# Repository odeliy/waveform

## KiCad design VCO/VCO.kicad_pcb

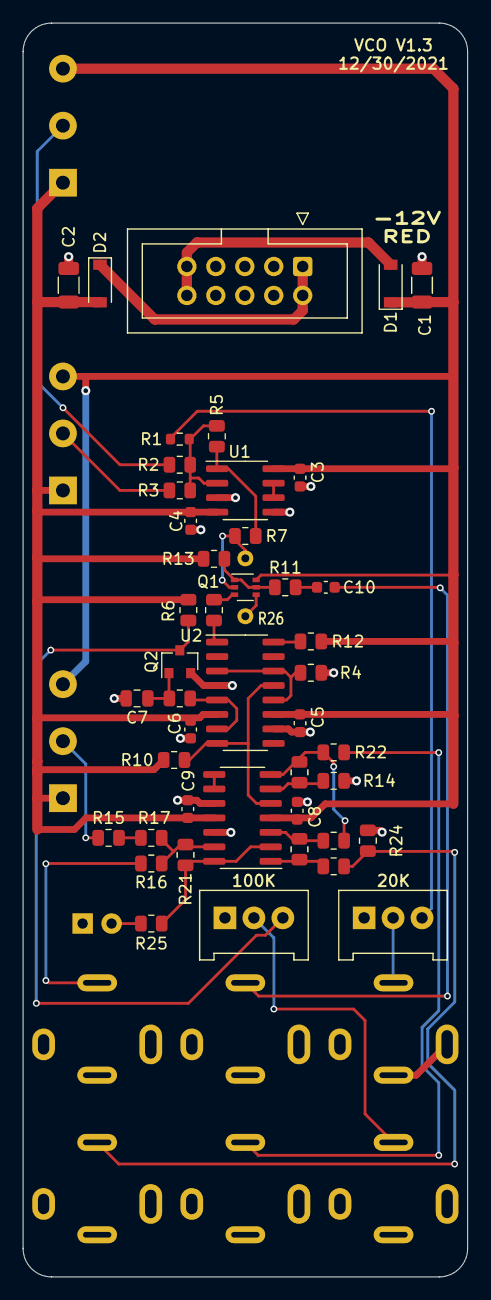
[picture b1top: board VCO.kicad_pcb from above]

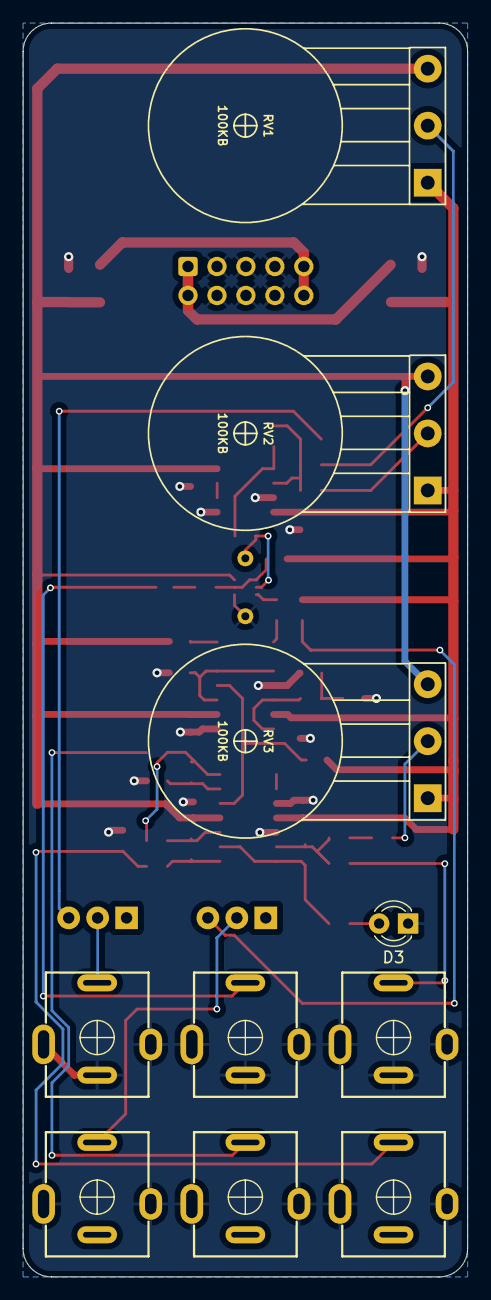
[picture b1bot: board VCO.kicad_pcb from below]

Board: 2 copper layers, 39.0 x 110.0 mm, 56 parts (10 on the bottom side), 38 nets.

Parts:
C1, C2: 10uF; C_1206_3216Metric
C3, C4, C5, C6, C8, C9, C10: 100nF; C_0603_1608Metric
C7: 3.3nF*; C_0805_2012Metric
D1, D2: SCH; D_SOD-123
D3: LED; LED_D3.0mm
J1: PWM; AudioJack_QingPu_WQP-PJ301BM_Vertical
J2: 1V_A; AudioJack_QingPu_WQP-PJ301BM_Vertical
J3: FM; AudioJack_QingPu_WQP-PJ301BM_Vertical
J4: SYNC; AudioJack_QingPu_WQP-PJ301BM_Vertical
J5: POWER; IDC-Header_2x05_P2.54mm_Vertical
J6: TRI; AudioJack_QingPu_WQP-PJ301BM_Vertical
J7: SQR; AudioJack_QingPu_WQP-PJ301BM_Vertical
Q1: BC847BPN; SOT-363_SC-70-6
Q2: MMBFJ112; SOT-23
R1: 91K; R_0603_1608Metric
R2: 330K; R_0805_2012Metric
R3: 10M; R_0805_2012Metric
R4: 5.6K; R_0805_2012Metric
R5, R6, R11, R21: 100K; R_0805_2012Metric
R7, R16: 56K; R_0805_2012Metric
R8, R15, R19: 12K; R_0805_2012Metric
R9: 680R; R_0805_2012Metric
R10, R14, R18: 10K; R_0805_2012Metric
R12: 47K; R_0805_2012Metric
R13, R20: 1M; R_0805_2012Metric
R17: 220K; R_0805_2012Metric
R22: 1K; R_0805_2012Metric
R23, R24, R25: 2K; R_0805_2012Metric
R26: 1K$; Specialty_tempco_paradox
RV1, RV2, RV3: 100KB; POT_16mm_detailed
RV4: 100KT*; TRIM_3296W_Alt
RV5: 20KT*; TRIM_3296W_Alt
U1: TL072; SOIC-8_3.9x4.9mm_P1.27mm
U2: LM13700; SOIC-16_3.9x9.9mm_P1.27mm
U3: TL074; SOIC-14_3.9x8.7mm_P1.27mm

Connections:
+12V: C1.1, C3.1, C5.1, C8.1, D1.1 (K), Q1.6 (C1), R12.1, RV1.3, RV2.3, RV3.3, U1.8 (V+), U2.11 (V+), U3.4 (V+)
-12V: C2.2, C4.2, C6.2, C9.2, D2.2 (A), R6.1, R10.2, R13.2, RV1.1, RV2.1, RV3.1, U1.4 (V-), U2.6 (V-), U3.11 (V-)
/1V_A: J2.T, RV5.2
/FINE: R3.2, RV2.2
/FM_lin: C10.2, J3.T
/FREQ: R2.2, RV1.2
/Iabc: Q1.3 (C2), R8.1
/LED: R21.1, R25.2, U3.2 (-), U3.14
/PW: R15.2, RV3.2
/PWM: J1.T, R16.2
/SQR: J7.T, R23.1, R24.2
/SYNC: J4.T, RV4.2
/TRI: J6.T, R22.1
/TRI_raw: R10.1, U2.8, U2.13 (-), U3.5 (+)
/V_expo: Q1.2 (B1), R7.1, R26.2
/tri2sqr: R18.2, R19.1, R22.2, U3.7
GND: C1.2, C2.1, C3.2, C4.1, C5.2, C6.1, C7.2, C8.2, C9.1, D3.1 (K), J1.S, J1.TN, J2.S, J2.TN, J3.S, J3.TN, J4.S, J5.3, J5.4, J5.5, J5.6, J5.7, J5.8, J6.S, J7.S, Q1.4 (E2), Q2.2 (S), R4.2, R14.2, R24.1, R26.1, U1.3 (+), U1.5 (+), U2.4 (-), U2.10, U3.10 (+), U3.12 (+)
unnamed: C7.1, Q2.1 (D), R9.2
unnamed: C10.1, R11.1
unnamed: D1.2 (A), J5.9, J5.10
unnamed: D2.1 (K), J5.1, J5.2
unnamed: D3.2 (A), R25.1
unnamed: Q1.1 (E1), Q1.5 (B2), R11.2, R13.1
unnamed: Q2.3 (G), R6.2, RV4.3
unnamed: R1.1, R2.1, R3.1, R5.2, U1.2 (-)
unnamed: R1.2, RV5.3
unnamed: R4.1, U2.3 (+), U2.12, U2.14 (+)
unnamed: R5.1, R7.2, U1.1
unnamed: R8.2, U2.1
unnamed: R9.1, U2.5, U2.7
unnamed: R12.2, U2.16
unnamed: R14.1, R19.2, U3.6 (-)
unnamed: R15.1, R17.2
unnamed: R16.1, R17.1, R21.2, U3.13 (-)
unnamed: R18.1, R20.2, U3.3 (+)
unnamed: R20.1, R23.2, U3.1
unnamed: U1.6 (-), U1.7
unnamed: U3.8, U3.9 (-)

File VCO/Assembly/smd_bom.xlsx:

Comment | Designator | Footprint | Part Ref.
100K | R5,R21,R11,R6 | R_0805_2012Metric | C17407
91K | R1 | R_0805_2012Metric | C137484
56K | R7,R16 | R_0805_2012Metric | C17756
2K | R25,R24,R23 | R_0805_2012Metric | C17604
1K | R22 | R_0805_2012Metric | C17513
1M | R20,R13 | R_0805_2012Metric | C17514
12K | R19,R15,R8 | R_0805_2012Metric | C17444
10K | R18,R14,R10 | R_0805_2012Metric | C17414
220K | R17 | R_0805_2012Metric | C17556
47K | R12 | R_0805_2012Metric | C17713
680R | R9 | R_0805_2012Metric | C17798
5.6K | R4 | R_0805_2012Metric | C4382
10M | R3 | R_0805_2012Metric | C26108
330K | R2 | R_0805_2012Metric | C17629
330pF | C11,C12 | C_0805_2012Metric | C51207
4.7pF | C13 | C_0805_2012Metric | C1820
100nF | C10,C9,C8,C6,C5,C4,C3 | C_0603 | C14663
3.3nF* | C7 | C_0805_2012Metric | C76473
10uF | C2,C1 | C_1206_3216Metric | C13585
BC847BPN | Q1 | SOT-363_SC-70-6 | C8655
MMBFJ112 | Q2 | SOT-23 | C258195
SCH | D2,D1 | D_SOD-123 | C8598
TL072 | U1 | SOIC-8_3.9x4.9mm_P1.27mm | C6961
TL074 | U3 | SOIC-14_3.9x8.7mm_P1.27mm | C12594
LM13700 | U2 | SOIC-16_3.9x9.9mm_P1.27mm | C174050

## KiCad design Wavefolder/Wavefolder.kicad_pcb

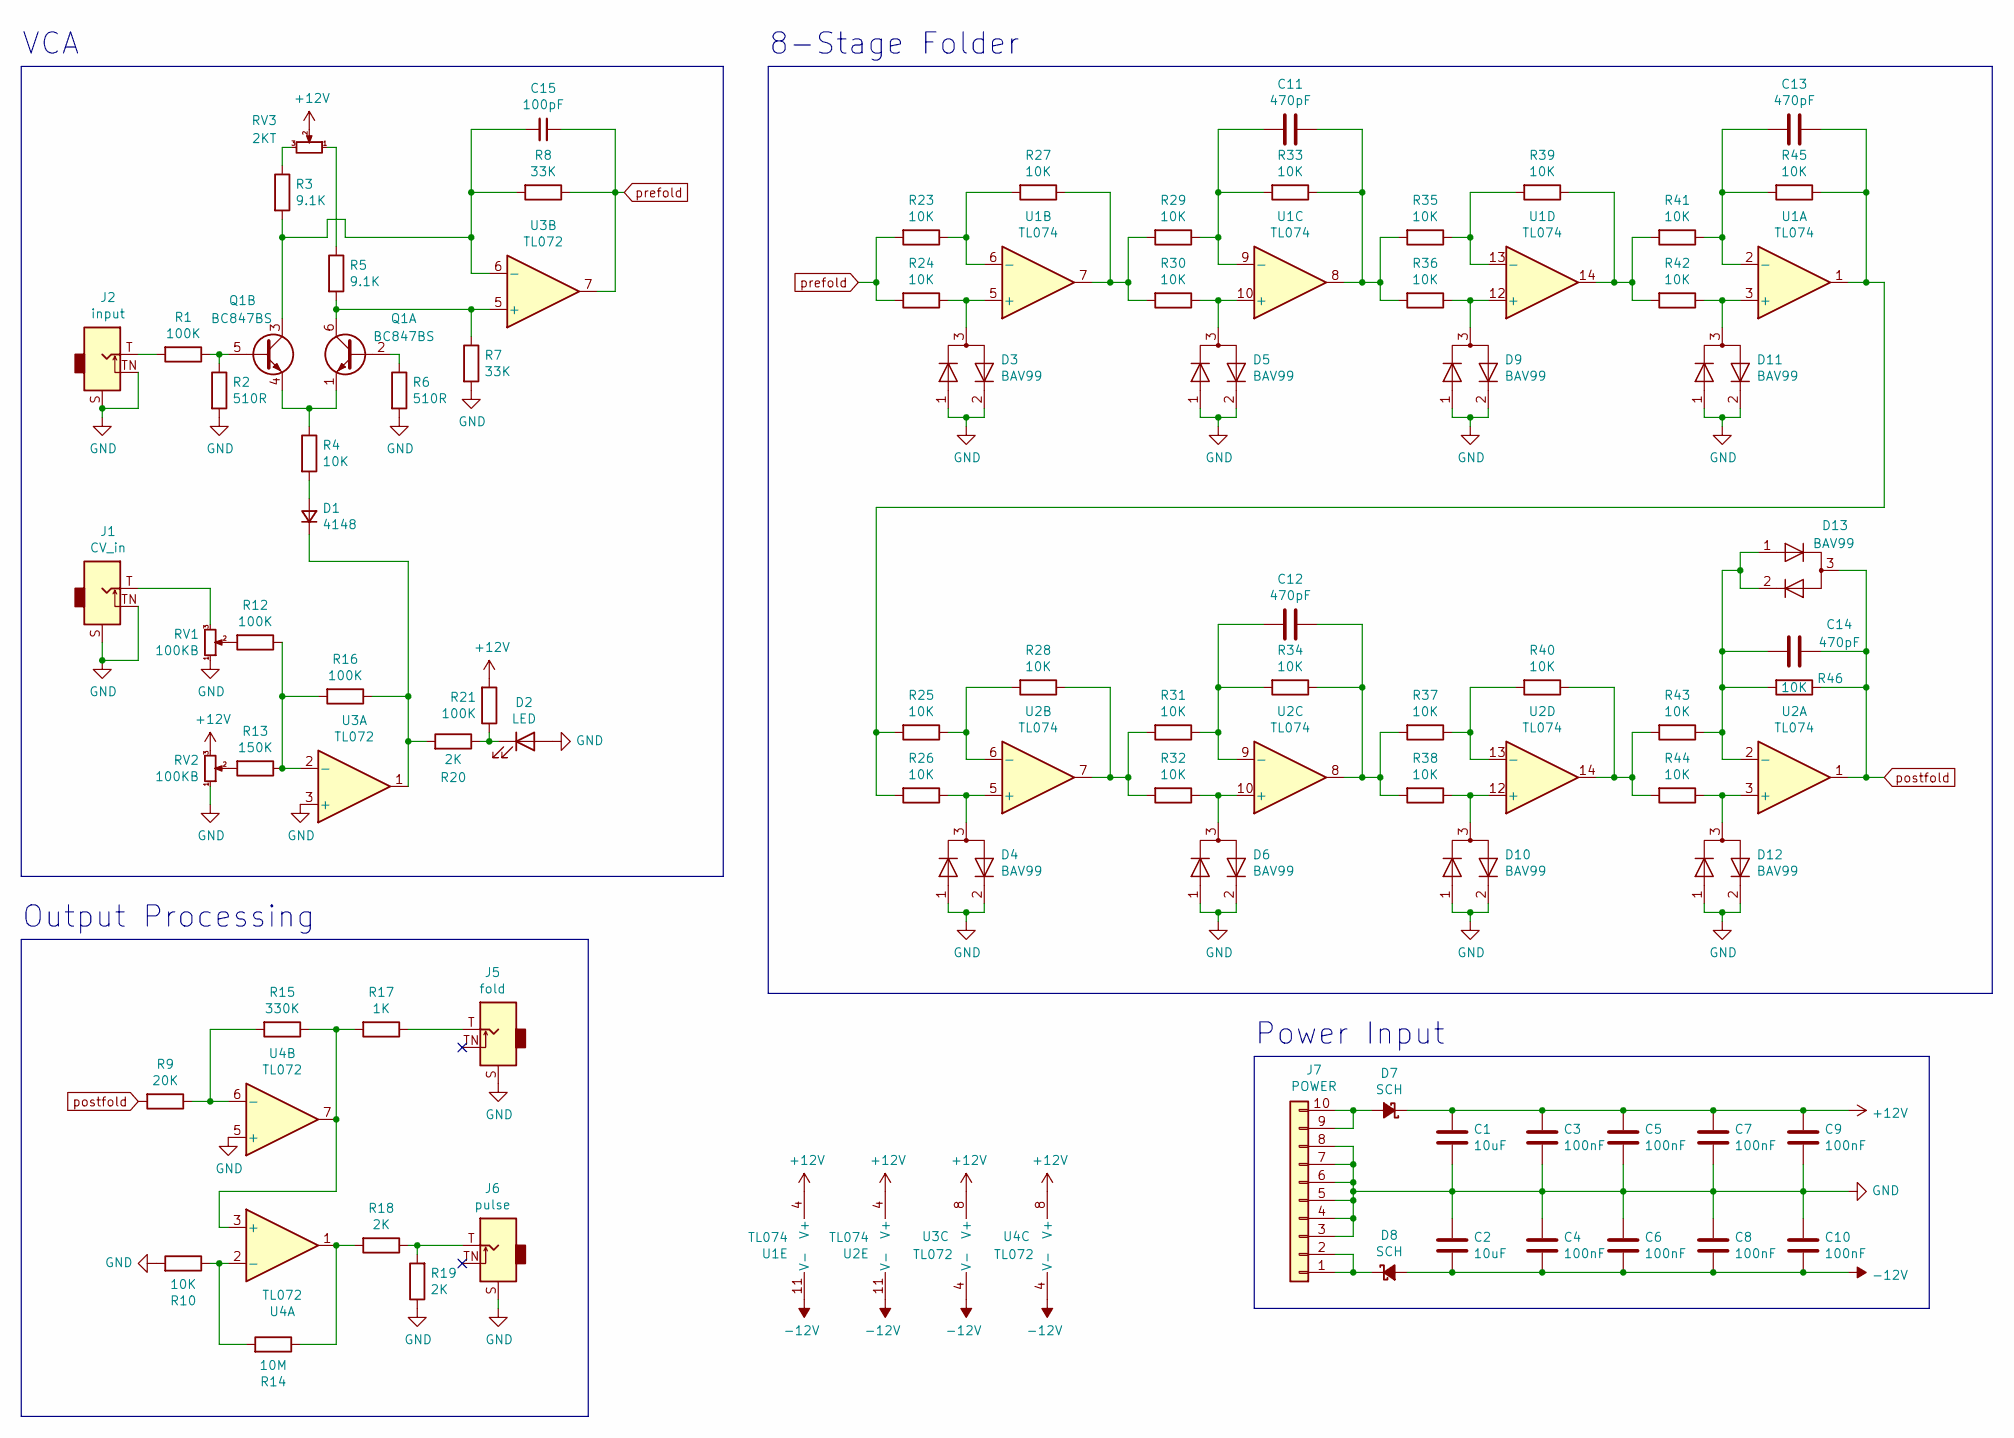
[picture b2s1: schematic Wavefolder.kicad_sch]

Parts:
C1, C2: 10uF; C_1206_3216Metric
C3, C4, C5, C6, C7, C8, C9, C10: 100nF; C_0603_1608Metric
C11, C12, C13, C14: 470pF; C_0805_2012Metric
C15: 100pF; C_0805_2012Metric
D1: 4148; D_SOD-123
D2: LED; LED_3mm
D3: BAV99; SOT-23; Part Ref C2500
D4, D5, D6, D9, D10, D11, D12, D13: BAV99; SOT-23; Part Ref C29718
D7, D8: SCH; D_SOD-123
J1: CV_in; AudioJack_QuPing_Pushfit
J2: input; AudioJack_QuPing_Pushfit
J5: fold; AudioJack_QuPing_Pushfit
J6: pulse; AudioJack_QuPing_Pushfit
J7: POWER; IDC-Header_2x05_P2.54mm_Vertical
Q1: BC847BS; SOT-363_SC-70-6
R1, R12, R16, R21: 100K; R_0805_2012Metric
R2, R6: 510R; R_0805_2012Metric
R3, R5: 9.1K; R_0805_2012Metric
R4, R10, R23, R24, R25, R26, R27, R28, R29, R30, R31, R32, R33, R34, R35, R36, R37, R38, R39, R40, R41, R42, R43, R44, R45, R46: 10K; R_0805_2012Metric
R7, R8: 33K; R_0805_2012Metric
R9: 20K; R_0805_2012Metric
R13: 150K; R_0805_2012Metric
R14: 10M; R_0805_2012Metric
R15: 330K; R_0805_2012Metric
R17: 1K; R_0805_2012Metric
R18, R19, R20: 2K; R_0805_2012Metric
RV1, RV2: 100KB; POT_16mm_detailed
RV3: 2KT; TRIM_3296W
U1, U2: TL074; SOIC-14_3.9x8.7mm_P1.27mm
U3, U4: TL072; SOIC-8_3.9x4.9mm_P1.27mm

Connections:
+12V: C1.1, C3.1, C5.1, C7.1, C9.1, D7.1 (K), R21.2, RV2.3, RV3.2, U1.4 (V+), U2.4 (V+), U3.8 (V+), U4.8 (V+)
-12V: C2.2, C4.2, C6.2, C8.2, C10.2, D8.2 (A), U1.11 (V-), U2.11 (V-), U3.4 (V-), U4.4 (V-)
GND: C1.2, C2.1, C3.2, C4.1, C5.2, C6.1, C7.2, C8.1, C9.2, C10.1, D2.2 (A), D3.1 (K), D3.2 (A), D4.1 (K), D4.2 (A), D5.1 (K), D5.2 (A), D6.1 (K), D6.2 (A), D9.1 (K), D9.2 (A), D10.1 (K), D10.2 (A), D11.1 (K), D11.2 (A), D12.1 (K), D12.2 (A), J1.S, J1.TN, J2.S, J2.TN, J5.S, J6.S, J7.3, J7.4, J7.5, J7.6, J7.7, J7.8, R2.2, R6.2, R7.2, R10.2, R19.1, RV1.1, RV2.1, U3.3 (+), U4.5 (+)
unnamed: C11.1, R33.1, R35.2, R36.2, U1.8
unnamed: C11.2, R29.1, R33.2, U1.9 (-)
unnamed: C12.1, R34.1, R37.2, R38.2, U2.8
unnamed: C12.2, R31.1, R34.2, U2.9 (-)
unnamed: C13.1, R25.2, R26.2, R45.1, U1.1
unnamed: C13.2, R41.1, R45.2, U1.2 (-)
unnamed: C14.2, D13.1 (K), D13.2 (A), R43.1, R46.2, U2.2 (-)
unnamed: C15.2, Q1.3 (C2), R3.2, R8.2, U3.6 (-)
unnamed: D1.1 (K), R16.1, R20.2, U3.1
unnamed: D1.2 (A), R4.2
unnamed: D2.1 (K), R20.1, R21.1
unnamed: D3.3 (K), R24.1, U1.5 (+)
unnamed: D4.3 (K), R26.1, U2.5 (+)
unnamed: D5.3 (K), R30.1, U1.10 (+)
unnamed: D6.3 (K), R32.1, U2.10 (+)
unnamed: D7.2 (A), J7.9, J7.10
unnamed: D8.1 (K), J7.1, J7.2
unnamed: D9.3 (K), R36.1, U1.12 (+)
unnamed: D10.3 (K), R38.1, U2.12 (+)
unnamed: D11.3 (K), R42.1, U1.3 (+)
unnamed: D12.3 (K), R44.1, U2.3 (+)
unnamed: J1.T, RV1.3
unnamed: J2.T, R1.2
unnamed: J5.T, R17.1
unnamed: J6.T, R18.1, R19.2
unnamed: Q1.5 (B2), R1.1, R2.1
unnamed: R3.1, RV3.3
unnamed: Q1.1 (E1), Q1.4 (E2), R4.1
unnamed: R5.1, RV3.1
unnamed: Q1.6 (C1), R5.2, R7.1, U3.5 (+)
unnamed: Q1.2 (B1), R6.1
unnamed: R10.1, R14.2, U4.2 (-)
unnamed: R12.1, R13.1, R16.2, U3.2 (-)
unnamed: R12.2, RV1.2
unnamed: R13.2, RV2.2
unnamed: R14.1, R18.2, U4.1
unnamed: R15.1, R17.2, U4.3 (+), U4.7
unnamed: R9.1, R15.2, U4.6 (-)
unnamed: R23.1, R27.2, U1.6 (-)
unnamed: R25.1, R28.2, U2.6 (-)
unnamed: R27.1, R29.2, R30.2, U1.7
unnamed: R28.1, R31.2, R32.2, U2.7
unnamed: R35.1, R39.2, U1.13 (-)
unnamed: R37.1, R40.2, U2.13 (-)
unnamed: R39.1, R41.2, R42.2, U1.14
unnamed: R40.1, R43.2, R44.2, U2.14
postfold: C14.1, D13.3 (K), R9.2, R46.1, U2.1
prefold: C15.1, R8.1, R23.2, R24.2, U3.7

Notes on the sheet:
VCA
8-Stage Folder
Output Processing
Power Input

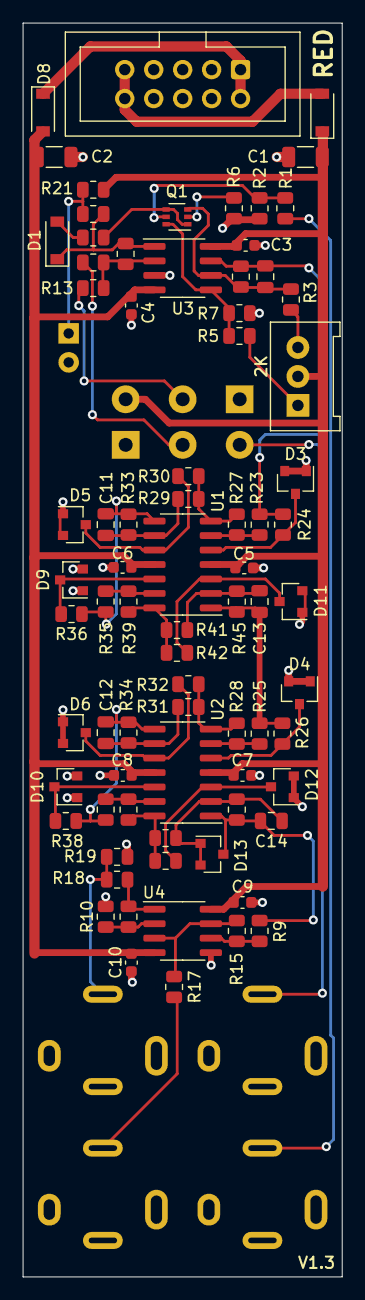
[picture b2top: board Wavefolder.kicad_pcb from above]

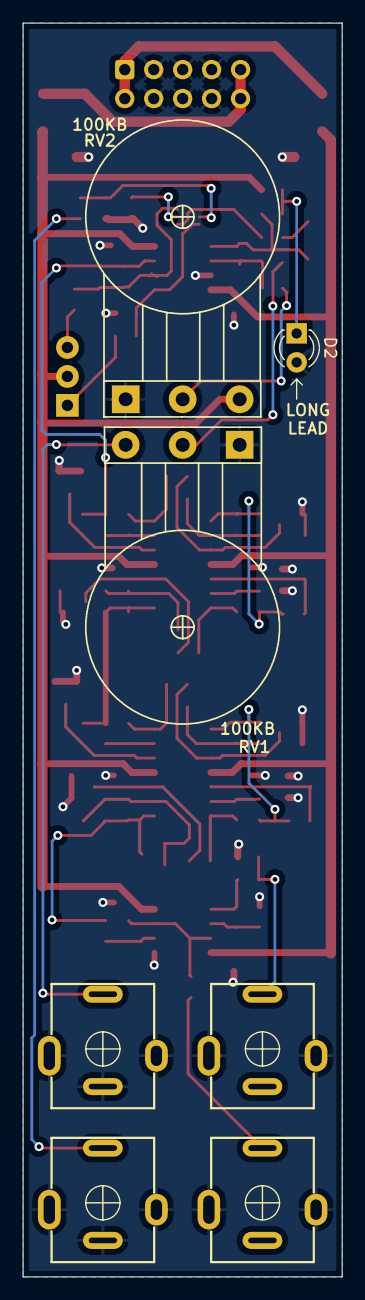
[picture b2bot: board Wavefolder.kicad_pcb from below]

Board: 2 copper layers, 28.0 x 110.0 mm, 85 parts (7 on the bottom side), 51 nets.

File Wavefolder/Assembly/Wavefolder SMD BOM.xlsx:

Comment | Designator | Footprint | Part Ref.
470pF | C13,C12,C11,C14 | C_0805_2012Metric | C1743
100nF | C4,C3,C10,C9,C8,C7,C6,C5 | C_0603_1608Metric | C14663
1N4148 | D1 | SOD-123 | C81598
BAV99 | D3,D12,D11,D10,D9,D6,D5,D4,D13 | SOT-23 | C2500
10K | R46,R45,R44,R43,R42,R41,R40,R39,R38,R37,R36,R35,R34,R33,R32,R31,R30,R29,R28,R27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 | R_0805_2012Metric | C17414
MMBT3904 | Q2,Q1 | SOT-23 | C20526
TL072 | U4,U3 | SOIC-8_3.9x4.9mm_P1.27mm | C6961
TL074 | U2,U1 | SOIC-14_3.9x8.7mm_P1.27mm | C12594
510R | R6,R2 | R_0805_2012Metric | C17734
100K | R21,R16,R12,R1 | R_0805_2012Metric | C17407
2K | R20,R19,R18 | R_0805_2012Metric | C17604
1K | R17 | R_0805_2012Metric | C17513
330K | R15 | R_0805_2012Metric | C17629
10M | R14 | R_0805_2012Metric | C26108
150K | R13 | R_0805_2012Metric | C17470
20K | R11,R9 | R_0805_2012Metric | C4328
33K | R8,R7 | R_0805_2012Metric | C17633
SCH | D8,D7 | D_SOD-123 | C8598
10uF | C2,C1 | C_1206_3216Metric | C13585
100pF | C15 | C_0805_2012Metric | C1790

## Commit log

2021-08-29 project added
2021-09-16 rev1 updates
2021-10-10 add digikey link for power headers
2021-11-08 rev 2 changes, see revision_log
2021-12-18 rev 3, see revision log
2021-12-18 added VCA stability cap
2021-12-30 rev 3 updates, see revision log
2022-01-12 remove clutter
